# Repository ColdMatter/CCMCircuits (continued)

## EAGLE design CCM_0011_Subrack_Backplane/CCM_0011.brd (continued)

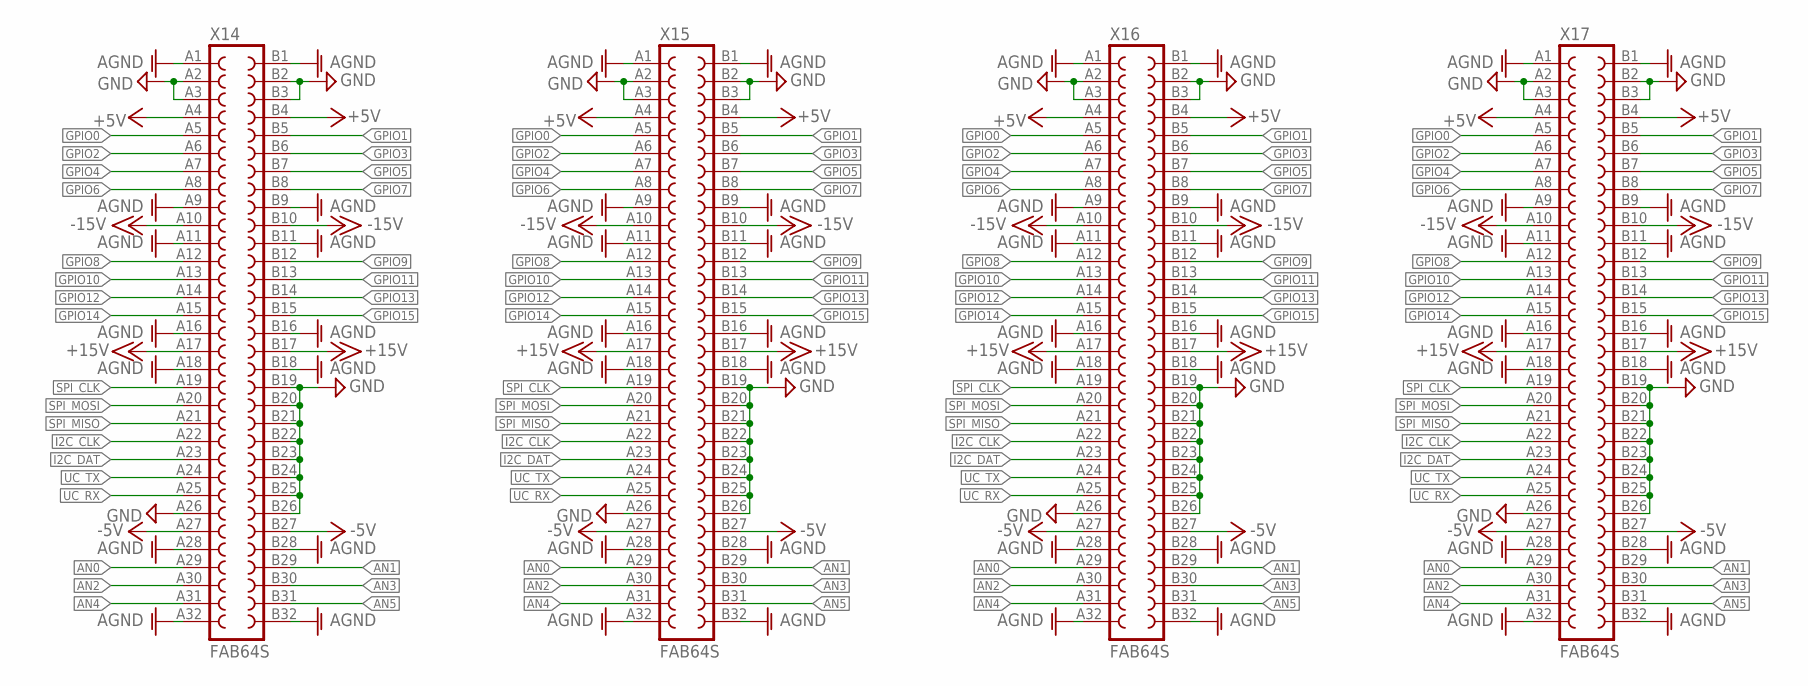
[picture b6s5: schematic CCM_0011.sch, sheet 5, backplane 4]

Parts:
X14, X15, X16, X17: FAB64S

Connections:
+5V: X14.A4, X14.B4, X15.A4, X15.B4, X16.A4, X16.B4, X17.A4, X17.B4; also elsewhere on the board
+15V: X14.A17, X14.B17, X15.A17, X15.B17, X16.A17, X16.B17, X17.A17, X17.B17; also elsewhere on the board
-5V: X14.A27, X14.B27, X15.A27, X15.B27, X16.A27, X16.B27, X17.A27, X17.B27; also elsewhere on the board
-15V: X14.A10, X14.B10, X15.A10, X15.B10, X16.A10, X16.B10, X17.A10, X17.B10; also elsewhere on the board
AGND: X14.A1, X14.A9, X14.A11, X14.A16, X14.A18, X14.A28, X14.A32, X14.B1, X14.B9, X14.B11, X14.B16, X14.B18, X14.B28, X14.B32, X15.A1, X15.A9, X15.A11, X15.A16, X15.A18, X15.A28, X15.A32, X15.B1, X15.B9, X15.B11, X15.B16, X15.B18, X15.B28, X15.B32, X16.A1, X16.A9, X16.A11, X16.A16, X16.A18, X16.A28, X16.A32, X16.B1, X16.B9, X16.B11, X16.B16, X16.B18, X16.B28, X16.B32, X17.A1, X17.A9, X17.A11, X17.A16, X17.A18, X17.A28, X17.A32, X17.B1, X17.B9, X17.B11, X17.B16, X17.B18, X17.B28, X17.B32; also elsewhere on the board
AN0: X14.A29, X15.A29, X16.A29, X17.A29; also elsewhere on the board
AN1: X14.B29, X15.B29, X16.B29, X17.B29; also elsewhere on the board
AN2: X14.A30, X15.A30, X16.A30, X17.A30; also elsewhere on the board
AN3: X14.B30, X15.B30, X16.B30, X17.B30; also elsewhere on the board
AN4: X14.A31, X15.A31, X16.A31, X17.A31; also elsewhere on the board
AN5: X14.B31, X15.B31, X16.B31, X17.B31; also elsewhere on the board
GND: X14.A2, X14.A3, X14.A26, X14.B2, X14.B3, X14.B19, X14.B20, X14.B21, X14.B22, X14.B23, X14.B24, X14.B25, X14.B26, X15.A2, X15.A3, X15.A26, X15.B2, X15.B3, X15.B19, X15.B20, X15.B21, X15.B22, X15.B23, X15.B24, X15.B25, X15.B26, X16.A2, X16.A3, X16.A26, X16.B2, X16.B3, X16.B19, X16.B20, X16.B21, X16.B22, X16.B23, X16.B24, X16.B25, X16.B26, X17.A2, X17.A3, X17.A26, X17.B2, X17.B3, X17.B19, X17.B20, X17.B21, X17.B22, X17.B23, X17.B24, X17.B25, X17.B26; also elsewhere on the board
GPIO0: X14.A5, X15.A5, X16.A5, X17.A5; also elsewhere on the board
GPIO1: X14.B5, X15.B5, X16.B5, X17.B5; also elsewhere on the board
GPIO2: X14.A6, X15.A6, X16.A6, X17.A6; also elsewhere on the board
GPIO3: X14.B6, X15.B6, X16.B6, X17.B6; also elsewhere on the board
GPIO4: X14.A7, X15.A7, X16.A7, X17.A7; also elsewhere on the board
GPIO5: X14.B7, X15.B7, X16.B7, X17.B7; also elsewhere on the board
GPIO6: X14.A8, X15.A8, X16.A8, X17.A8; also elsewhere on the board
GPIO7: X14.B8, X15.B8, X16.B8, X17.B8; also elsewhere on the board
GPIO8: X14.A12, X15.A12, X16.A12, X17.A12; also elsewhere on the board
GPIO9: X14.B12, X15.B12, X16.B12, X17.B12; also elsewhere on the board
GPIO10: X14.A13, X15.A13, X16.A13, X17.A13; also elsewhere on the board
GPIO11: X14.B13, X15.B13, X16.B13, X17.B13; also elsewhere on the board
GPIO12: X14.A14, X15.A14, X16.A14, X17.A14; also elsewhere on the board
GPIO13: X14.B14, X15.B14, X16.B14, X17.B14; also elsewhere on the board
GPIO14: X14.A15, X15.A15, X16.A15, X17.A15; also elsewhere on the board
GPIO15: X14.B15, X15.B15, X16.B15, X17.B15; also elsewhere on the board
I2C_CLK: X14.A22, X15.A22, X16.A22, X17.A22; also elsewhere on the board
I2C_DAT: X14.A23, X15.A23, X16.A23, X17.A23; also elsewhere on the board
SPI_CLK: X14.A19, X15.A19, X16.A19, X17.A19; also elsewhere on the board
SPI_MISO: X14.A21, X15.A21, X16.A21, X17.A21; also elsewhere on the board
SPI_MOSI: X14.A20, X15.A20, X16.A20, X17.A20; also elsewhere on the board
UC_RX: X14.A25, X15.A25, X16.A25, X17.A25; also elsewhere on the board
UC_TX: X14.A24, X15.A24, X16.A24, X17.A24; also elsewhere on the board

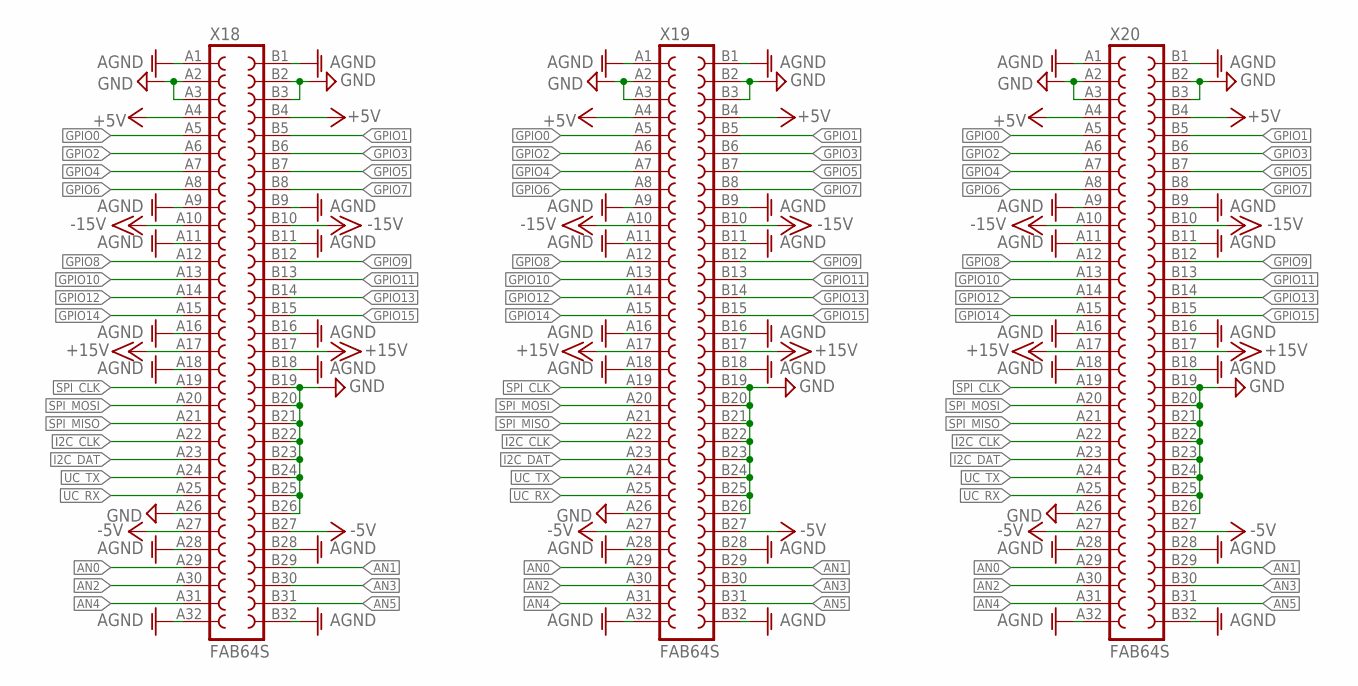
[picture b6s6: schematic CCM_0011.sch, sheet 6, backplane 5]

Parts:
X18, X19, X20: FAB64S

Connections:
+5V: X18.A4, X18.B4, X19.A4, X19.B4, X20.A4, X20.B4; also elsewhere on the board
+15V: X18.A17, X18.B17, X19.A17, X19.B17, X20.A17, X20.B17; also elsewhere on the board
-5V: X18.A27, X18.B27, X19.A27, X19.B27, X20.A27, X20.B27; also elsewhere on the board
-15V: X18.A10, X18.B10, X19.A10, X19.B10, X20.A10, X20.B10; also elsewhere on the board
AGND: X18.A1, X18.A9, X18.A11, X18.A16, X18.A18, X18.A28, X18.A32, X18.B1, X18.B9, X18.B11, X18.B16, X18.B18, X18.B28, X18.B32, X19.A1, X19.A9, X19.A11, X19.A16, X19.A18, X19.A28, X19.A32, X19.B1, X19.B9, X19.B11, X19.B16, X19.B18, X19.B28, X19.B32, X20.A1, X20.A9, X20.A11, X20.A16, X20.A18, X20.A28, X20.A32, X20.B1, X20.B9, X20.B11, X20.B16, X20.B18, X20.B28, X20.B32; also elsewhere on the board
AN0: X18.A29, X19.A29, X20.A29; also elsewhere on the board
AN1: X18.B29, X19.B29, X20.B29; also elsewhere on the board
AN2: X18.A30, X19.A30, X20.A30; also elsewhere on the board
AN3: X18.B30, X19.B30, X20.B30; also elsewhere on the board
AN4: X18.A31, X19.A31, X20.A31; also elsewhere on the board
AN5: X18.B31, X19.B31, X20.B31; also elsewhere on the board
GND: X18.A2, X18.A3, X18.A26, X18.B2, X18.B3, X18.B19, X18.B20, X18.B21, X18.B22, X18.B23, X18.B24, X18.B25, X18.B26, X19.A2, X19.A3, X19.A26, X19.B2, X19.B3, X19.B19, X19.B20, X19.B21, X19.B22, X19.B23, X19.B24, X19.B25, X19.B26, X20.A2, X20.A3, X20.A26, X20.B2, X20.B3, X20.B19, X20.B20, X20.B21, X20.B22, X20.B23, X20.B24, X20.B25, X20.B26; also elsewhere on the board
GPIO0: X18.A5, X19.A5, X20.A5; also elsewhere on the board
GPIO1: X18.B5, X19.B5, X20.B5; also elsewhere on the board
GPIO2: X18.A6, X19.A6, X20.A6; also elsewhere on the board
GPIO3: X18.B6, X19.B6, X20.B6; also elsewhere on the board
GPIO4: X18.A7, X19.A7, X20.A7; also elsewhere on the board
GPIO5: X18.B7, X19.B7, X20.B7; also elsewhere on the board
GPIO6: X18.A8, X19.A8, X20.A8; also elsewhere on the board
GPIO7: X18.B8, X19.B8, X20.B8; also elsewhere on the board
GPIO8: X18.A12, X19.A12, X20.A12; also elsewhere on the board
GPIO9: X18.B12, X19.B12, X20.B12; also elsewhere on the board
GPIO10: X18.A13, X19.A13, X20.A13; also elsewhere on the board
GPIO11: X18.B13, X19.B13, X20.B13; also elsewhere on the board
GPIO12: X18.A14, X19.A14, X20.A14; also elsewhere on the board
GPIO13: X18.B14, X19.B14, X20.B14; also elsewhere on the board
GPIO14: X18.A15, X19.A15, X20.A15; also elsewhere on the board
GPIO15: X18.B15, X19.B15, X20.B15; also elsewhere on the board
I2C_CLK: X18.A22, X19.A22, X20.A22; also elsewhere on the board
I2C_DAT: X18.A23, X19.A23, X20.A23; also elsewhere on the board
SPI_CLK: X18.A19, X19.A19, X20.A19; also elsewhere on the board
SPI_MISO: X18.A21, X19.A21, X20.A21; also elsewhere on the board
SPI_MOSI: X18.A20, X19.A20, X20.A20; also elsewhere on the board
UC_RX: X18.A25, X19.A25, X20.A25; also elsewhere on the board
UC_TX: X18.A24, X19.A24, X20.A24; also elsewhere on the board

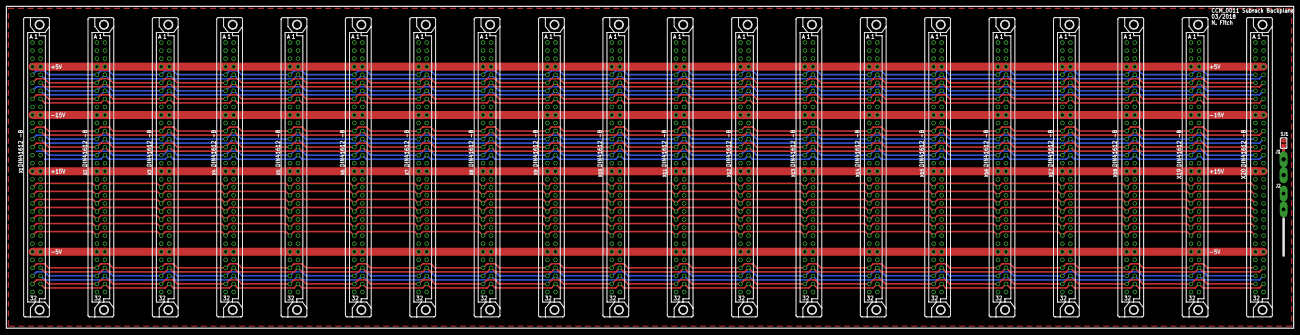
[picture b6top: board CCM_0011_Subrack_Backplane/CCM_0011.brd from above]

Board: 2 copper layers, 406.4 x 101.6 mm, 23 parts (0 on the bottom side), 35 nets.
